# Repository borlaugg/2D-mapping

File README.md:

# 2D-mapping
This is the repository for the EE-344 EDL course project - 2D mapping using iPEC probe with the PCB design and code used

Done by-
Keshav, Mudit and Rishabh

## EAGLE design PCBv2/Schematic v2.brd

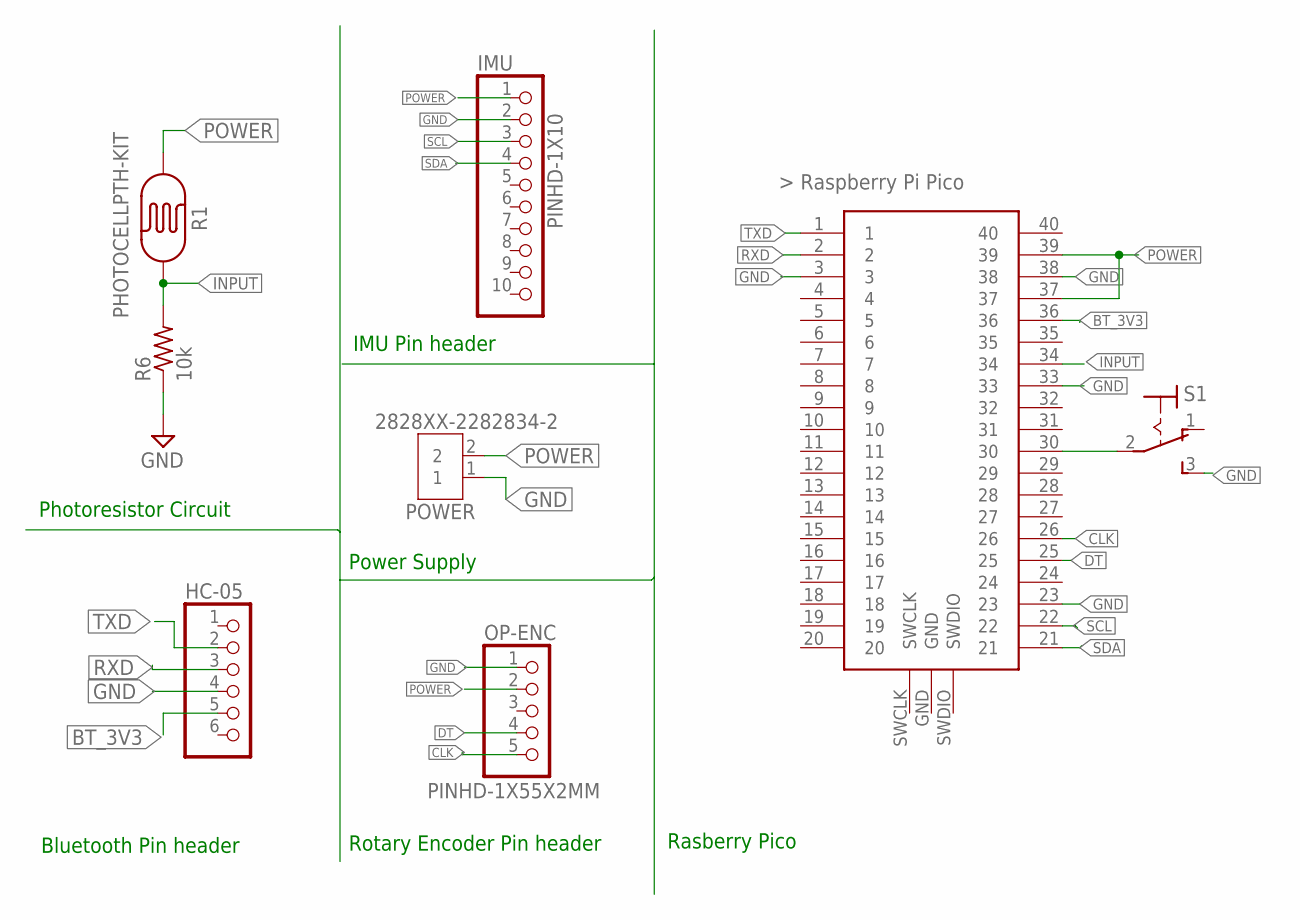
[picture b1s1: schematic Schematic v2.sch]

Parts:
HC-05: PINHD-1X6; 1X06
IMU: PINHD-1X10; 1X10-BIG
OP-ENC: PINHD-1X55X2MM; 1_05X2MM
PICO: RASPBERRY-PI-PICO_TH; FT_RASPBERRY-PI-PICO_TH
POWER: 2828XX-2282834-2; TERMBLK_254-2N
R1: PHOTOCELLPTH-KIT; PHOTOCELL-KIT
R6: 10k; 0207/10
S1: 320-916

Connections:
BT_3V3: HC-05.5, PICO.36
CLK: OP-ENC.5, PICO.26
DT: OP-ENC.4, PICO.25
GND: HC-05.4, IMU.2, OP-ENC.1, PICO.3, PICO.23, PICO.33, PICO.38, POWER.1, R6.1, S1.3 (S)
INPUT: PICO.34, R1.1, R6.2
unnamed: PICO.30, S1.2
POWER: IMU.1, OP-ENC.2, PICO.37, PICO.39, POWER.2, R1.2
RXD: HC-05.3, PICO.2
SCL: IMU.3, PICO.22
SDA: IMU.4, PICO.21
TXD: HC-05.2, PICO.1

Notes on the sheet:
Photoresistor Circuit
IMU Pin header
Rotary Encoder Pin header
Bluetooth Pin header
Power Supply
Rasberry Pico

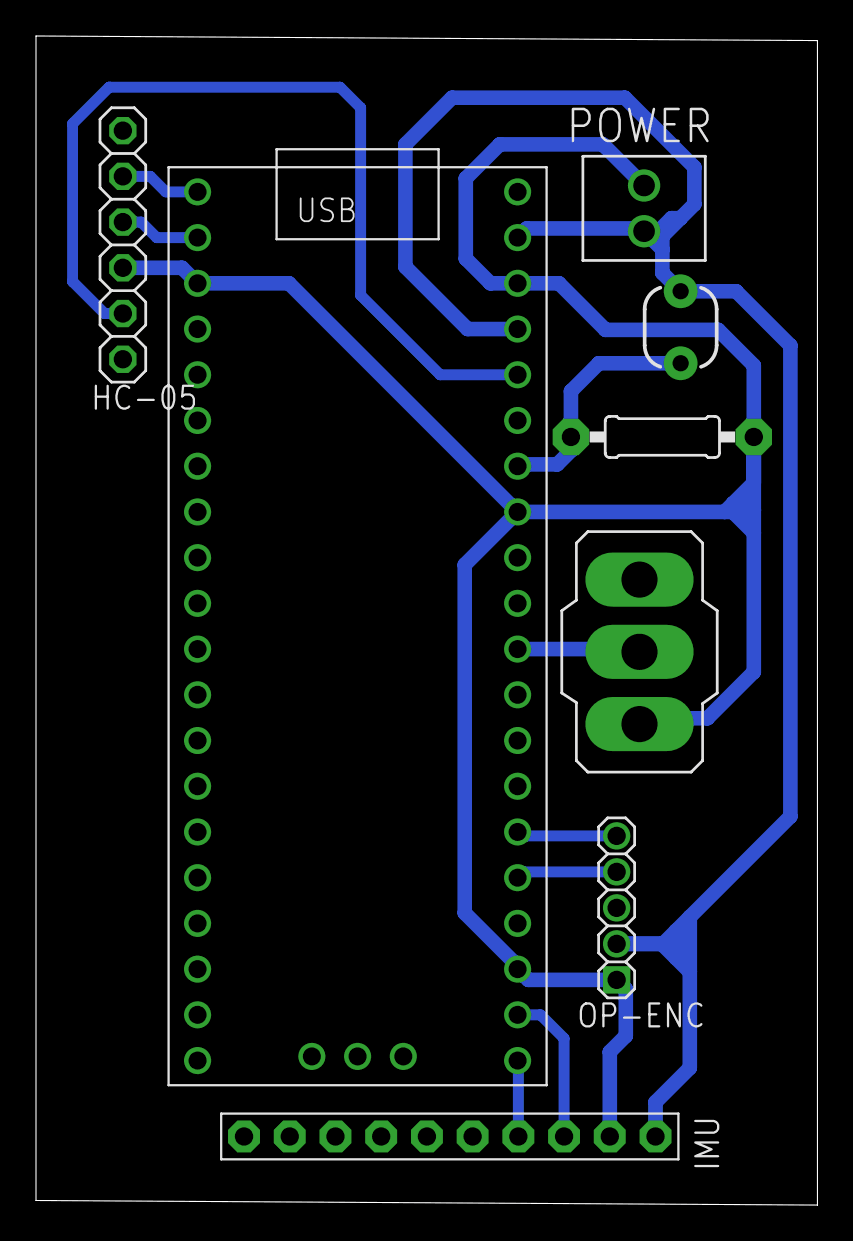
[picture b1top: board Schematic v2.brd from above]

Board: 2 copper layers, 43.4 x 64.9 mm, 8 parts (0 on the bottom side), 11 nets.

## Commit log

2023-02-14 added libraries
2023-03-26 Final board
2023-03-26 Added code
2023-03-26 added dimensions
2023-04-09 added board without gnd plane

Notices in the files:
parts and their libraries:
SparkFun-Sensors: Licensing: CC v3.0 Share-Alike You are welcome to use this library for commercial purposes.
